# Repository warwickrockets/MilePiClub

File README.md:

# MilePiClub
Warwick Rockets and UWCS High Altitude Ballooning

TODO:
* pi -> camera 		<< mcnutty
* pi -> gps			<< ed, alex
* pi -> gsm			<< rhiba
* pi -> rays			<< rockets person
* pi -> parachute		<< josh, alex
* pi -> radio			<< rayhaan
* SDR 				<< rayhaan
* main application	<< uncle tom cobley
* balloon				<< emre
* launch auth			<< rob

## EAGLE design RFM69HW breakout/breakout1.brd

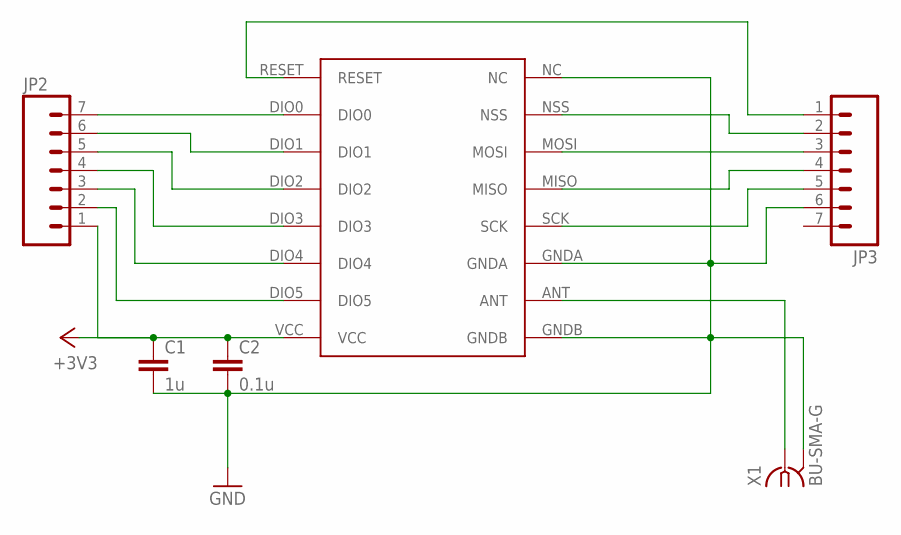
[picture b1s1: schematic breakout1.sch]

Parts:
C1: 1u; 1206
C2: 0.1u; 1206
JP2, JP3: M07LOCK; 1X07_LOCK
U$1: RFM69HW; RFM
X1: BU-SMA-G

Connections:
+3V3: C1.1, C2.1, JP2.1, U$1.VCC
GND: C1.2, C2.2, JP3.6, U$1.GNDA, U$1.GNDB, U$1.NC, X1.2, X1.3 (2), X1.4 (2), X1.5 (2)
unnamed: U$1.ANT, X1.1
unnamed: JP3.2, U$1.NSS
unnamed: JP3.3, U$1.MOSI
unnamed: JP3.4, U$1.MISO
unnamed: JP3.5, U$1.SCK
unnamed: JP2.2, U$1.DIO5
unnamed: JP2.3, U$1.DIO4
unnamed: JP2.7, U$1.DIO0
unnamed: JP3.1, U$1.RESET
unnamed: JP2.4, U$1.DIO3
unnamed: JP2.5, U$1.DIO2
unnamed: JP2.6, U$1.DIO1

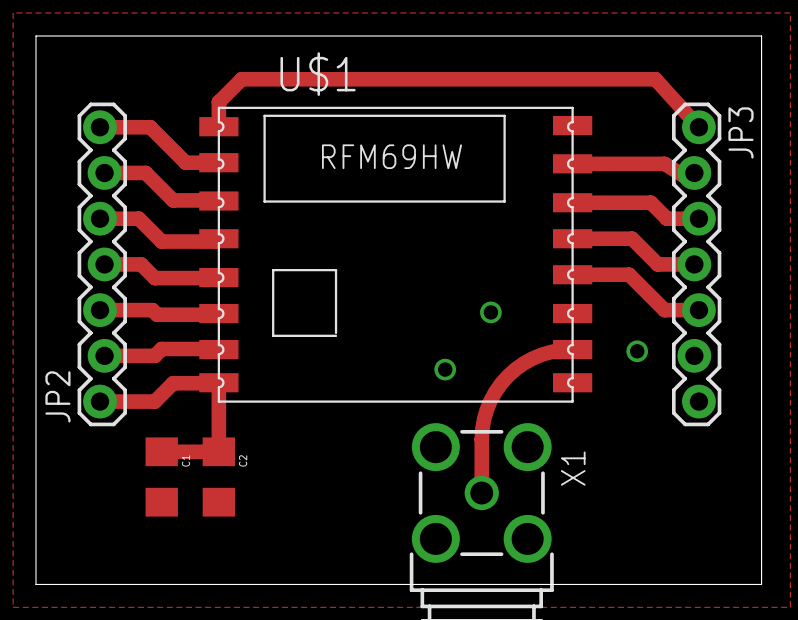
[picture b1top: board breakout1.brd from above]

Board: 2 copper layers, 40.3 x 30.5 mm, 6 parts (0 on the bottom side), 14 nets.

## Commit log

2015-03-03 Efforts so far
    Basic scripts for the modules we're using.
2015-03-04 +todo
    added list of jobs
2015-03-04 format
    maybe github will render this less terribly?
2015-03-22 Basic description of sending an SMS via the GSM module.
2015-03-22 .gitignore for vim temp files
2015-03-22 Existing Python code implementation added for reference
2015-03-22 Add serial library
2015-03-22 Realised it was possible to use ctrl+z to send 0x1A
2015-03-22 Basic c++ class to send SMS, will be expanded and improved in future
2015-04-02 Tweaked readme formatting again
    Well, this thing with an unordered list seems to work ok. I hope.
2015-04-10 Started work on MPC's RFM69HW breakout
    This version will probably break out eight pins for SPI, power, and
    interrupts. Very little actually done so far.
    Also added .gitignore for Eagle backup files.
2015-06-14 Finished the RFM69HW breakout
    (I think so anyway. Wasn't sure which DIO pins to break out, so broke
    out all of them! :) )
2015-06-14 Tweaked pin spacing
    It'd probably be nice if the thing could be stuck in a breadboard!
2015-06-14 Fiddled with via fence
    Because, y'know, that'll make all the difference

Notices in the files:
parts and their libraries:
SparkFun: Licensing: CC v3.0 Share-Alike You are welcome to use this library for commercial purposes.
